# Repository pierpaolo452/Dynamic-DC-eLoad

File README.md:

# Dynamic DC eLoad
A DC electronic load with protections. It's a learning/developing project, so a lot of things are discrete just for learning to build it for example the Efuse is discrete

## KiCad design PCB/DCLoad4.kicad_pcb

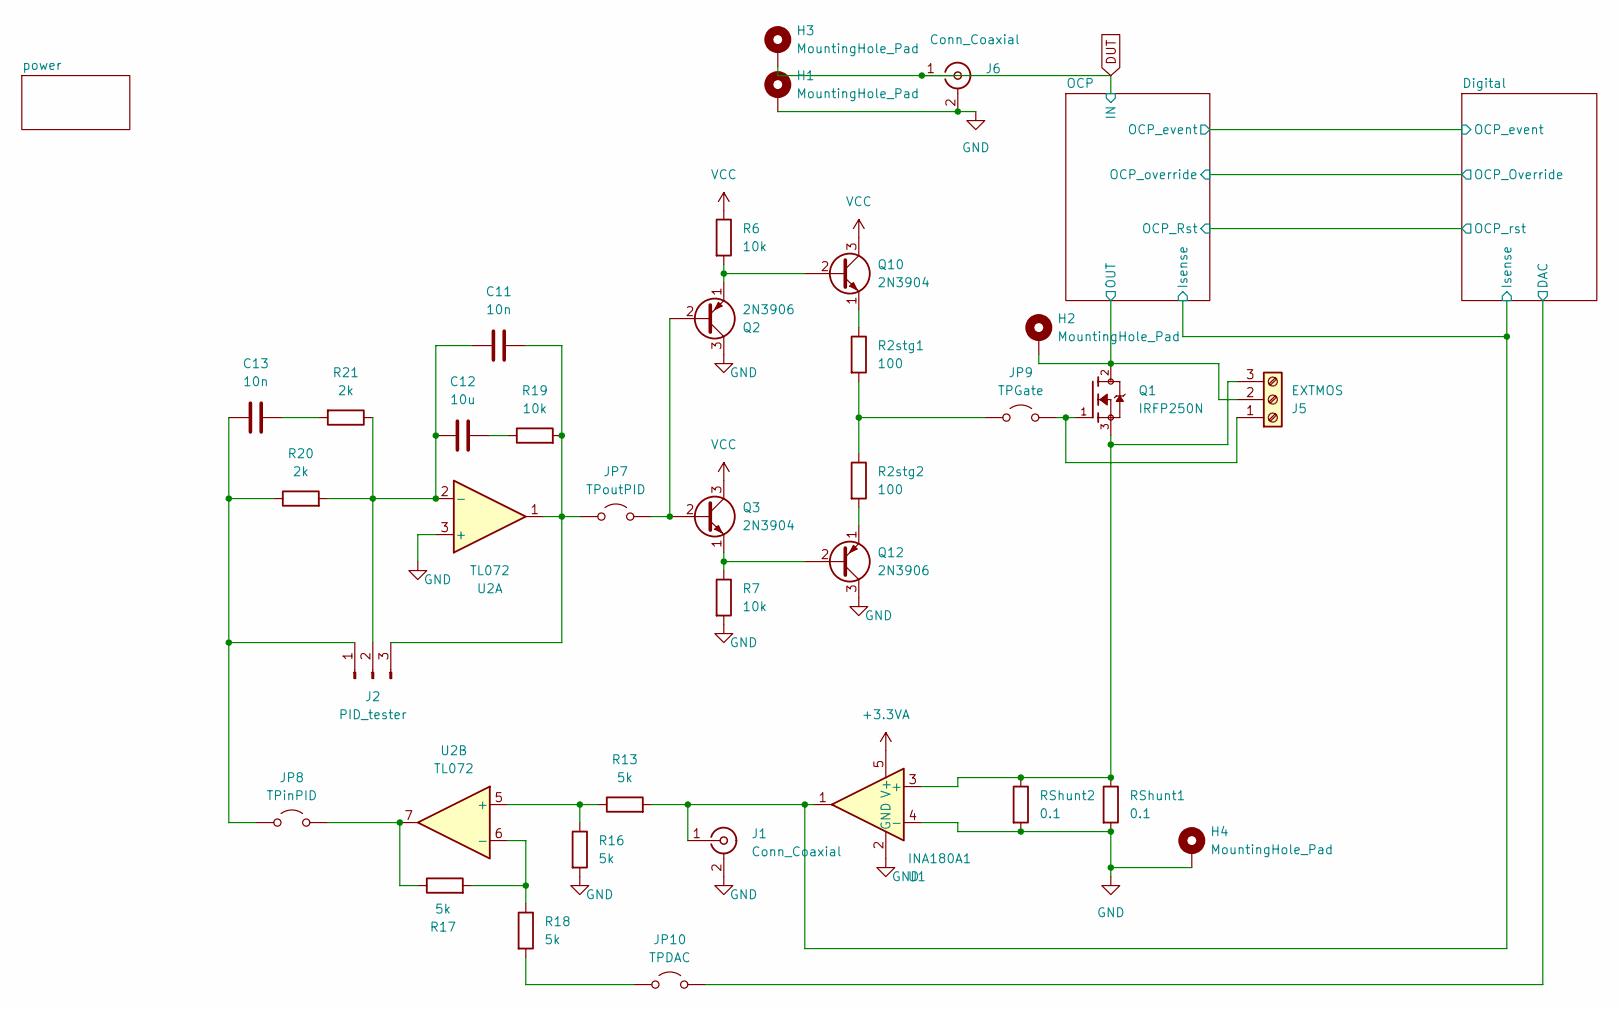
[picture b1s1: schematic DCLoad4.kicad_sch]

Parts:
C11, C13: 10n; C_0805_2012Metric_Pad1.18x1.45mm_HandSolder
C12: 10u; C_0805_2012Metric_Pad1.18x1.45mm_HandSolder
H1, H2, H3, H4: MountingHole_Pad; MountingHole_3.7mm_Pad_Via
J1, J6: Conn_Coaxial; BNC_Amphenol_B6252HB-NPP3G-50_Horizontal
J2: PID_tester; PinSocket_1x03_P2.54mm_Vertical
J5: EXTMOS; TerminalBlock_Phoenix_MKDS-1,5-3-5.08_1x03_P5.08mm_Horizont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
JP7: TPoutPID; PinSocket_1x02_P2.54mm_Vertical
JP8: TPinPID; PinSocket_1x02_P2.54mm_Vertical
JP9: TPGate; PinSocket_1x02_P2.54mm_Vertical
JP10: TPDAC; PinSocket_1x02_P2.54mm_Vertical
Q1: IRFP250N; TO-247-3_Vertical
Q2: 2N3906; SOT-23_Handsoldering
Q3: 2N3904; SOT-23_Handsoldering
Q10: 2N3904; TO-92
Q12: 2N3906; TO-92
R2stg1, R2stg2: 100; R_2512_6332Metric_Pad1.40x3.35mm_HandSolder
R6, R7, R19: 10k; R_0805_2012Metric_Pad1.20x1.40mm_HandSolder
R13, R16, R17, R18: 5k; R_0805_2012Metric_Pad1.20x1.40mm_HandSolder
R20, R21: 2k; R_0805_2012Metric_Pad1.20x1.40mm_HandSolder
RShunt1, RShunt2: 0.1; R_2512_6332Metric_Pad1.40x3.35mm_HandSolder
U1: INA180A1; SOT-23-5_HandSoldering
U2: TL072; DIP-8_W7.62mm_Socket

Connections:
+3.3VA: U1.5 (V+); also elsewhere on the board
/Digital/DAC: JP10.2 (B); also elsewhere on the board
/Digital/Isense: J1.1 (In), R13.2, U1.1; also elsewhere on the board
/OCP/OUT: H2.1, J5.2, Q1.2; also elsewhere on the board
DUT: H3.1, J6.1 (In); also elsewhere on the board
GND: H1.1, H4.1, J1.2 (Ext), J6.2 (Ext), Q2.3 (C), Q12.3 (C), R7.2, R16.2, RShunt1.2, RShunt2.2, U1.2 (GND), U1.4 (-), U2.3 (+); also elsewhere on the board
unnamed: C12.2, R19.1
unnamed: C13.2, R21.2
unnamed: C13.1, J2.1, JP8.1 (A), R20.1
unnamed: C11.1, C12.1, J2.2, R20.2, R21.1, U2.2 (-)
unnamed: C11.2, J2.3, JP7.1 (A), R19.2, U2.1
unnamed: J5.1, JP9.2 (B), Q1.1
unnamed: J5.3, Q1.3, RShunt1.1, RShunt2.1, U1.3 (+)
unnamed: JP7.2 (B), Q2.2 (B), Q3.2 (B)
unnamed: JP8.2 (B), R17.1, U2.7
unnamed: JP9.1 (A), R2stg1.2, R2stg2.1
unnamed: JP10.1 (A), R18.2
unnamed: Q2.1 (E), Q10.2 (B), R6.2
unnamed: Q10.1 (E), R2stg1.1
unnamed: Q3.1 (E), Q12.2 (B), R7.1
unnamed: Q12.1 (E), R2stg2.2
unnamed: R13.1, R16.1, U2.5 (+)
unnamed: R17.2, R18.1, U2.6 (-)
VCC: Q3.3 (C), Q10.3 (C), R6.1; also elsewhere on the board

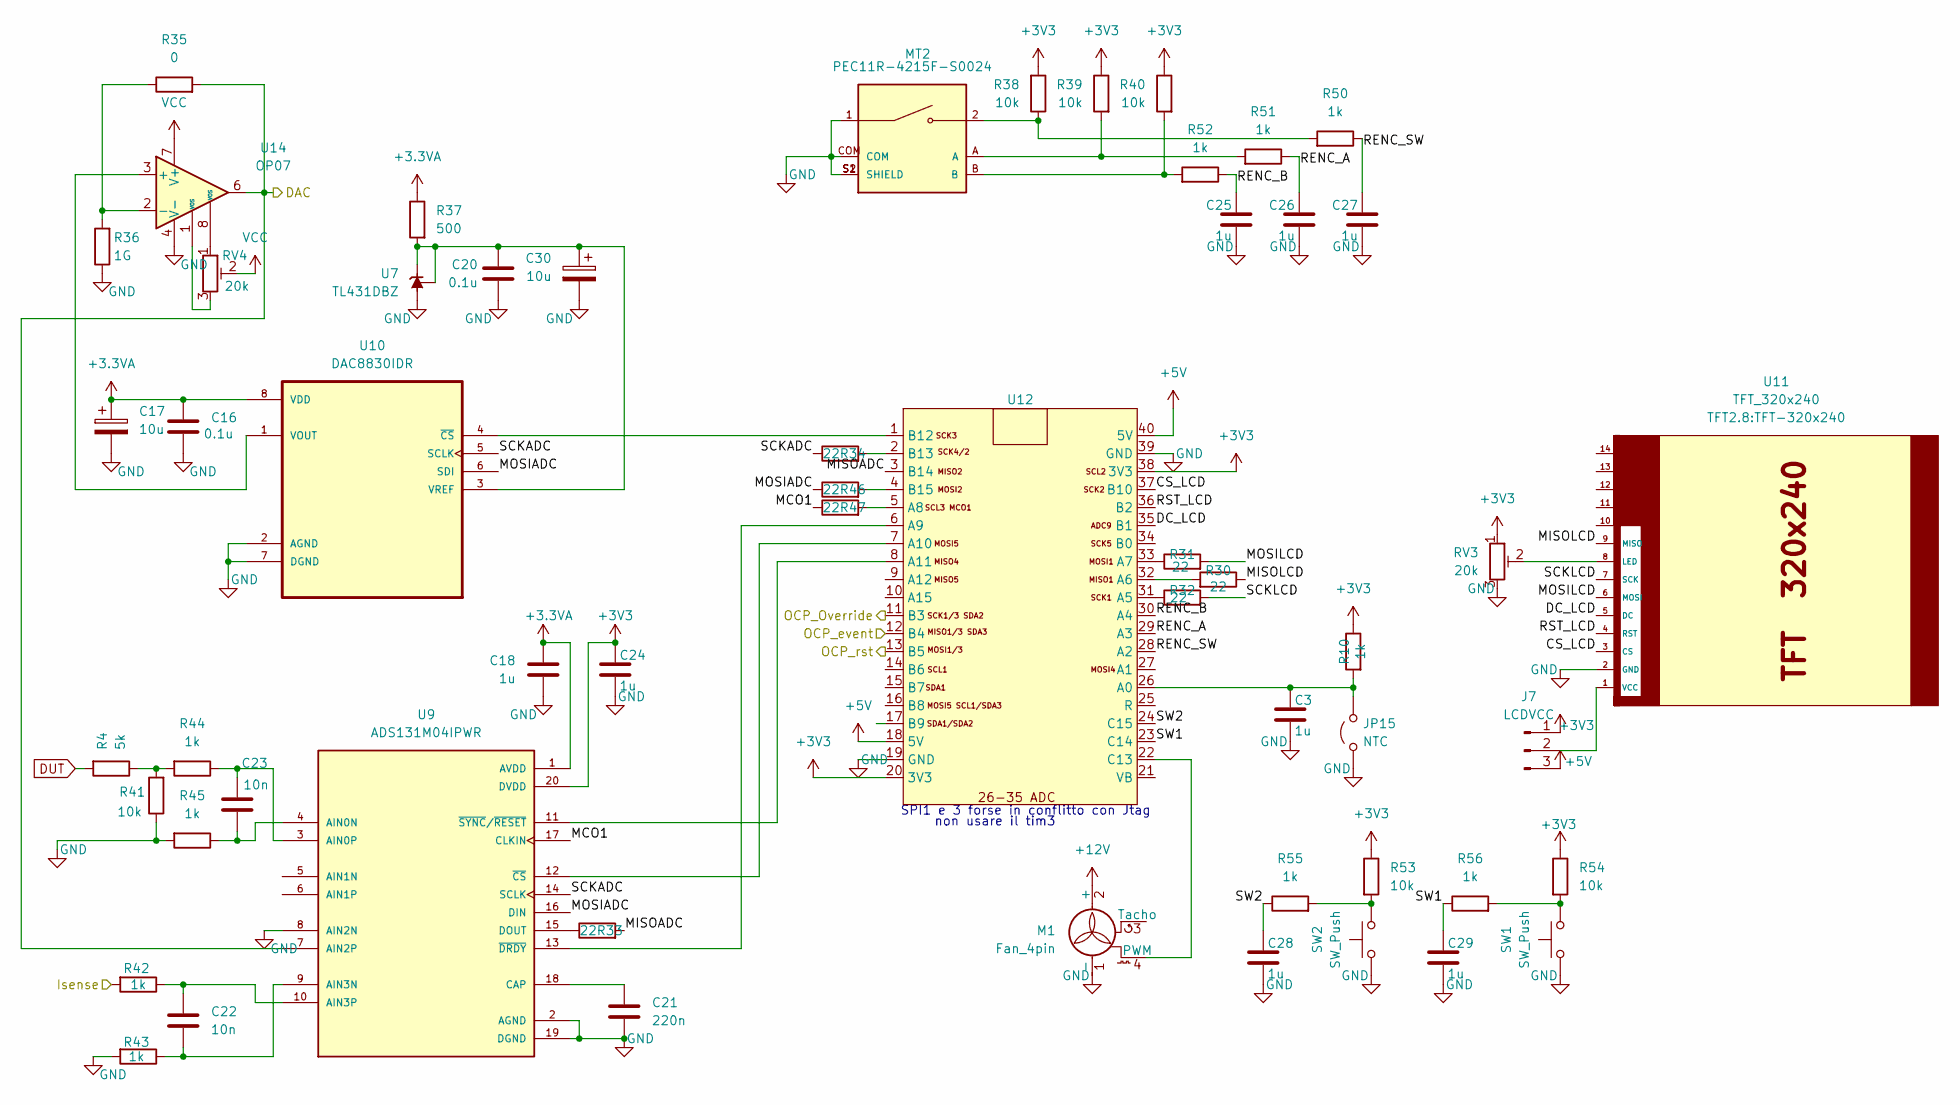
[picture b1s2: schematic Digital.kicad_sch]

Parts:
C3, C18, C24, C25, C26, C27, C28, C29: 1u; C_0805_2012Metric_Pad1.18x1.45mm_HandSolder
C16, C20: 0.1u; C_0805_2012Metric_Pad1.18x1.45mm_HandSolder
C17, C30: 10u; CP_EIA-3216-18_Kemet-A_Pad1.58x1.35mm_HandSolder
C21: 220n; C_0805_2012Metric_Pad1.18x1.45mm_HandSolder
C22, C23: 10n; C_0805_2012Metric_Pad1.18x1.45mm_HandSolder
J7: LCDVCC; PinSocket_1x03_P2.54mm_Vertical
JP15: NTC; PinSocket_1x02_P2.54mm_Vertical
M1: Fan_4pin; FanPinHeader_1x04_P2.54mm_Vertical
MT2: PEC11R-4215F-S0024; XDCR_PEC11R-4215F-S0024; PARTREV Rev. 09/19
R4: 5k; R_0805_2012Metric_Pad1.20x1.40mm_HandSolder
R10, R42, R43, R44, R45, R50, R51, R52, R55, R56: 1k; R_0805_2012Metric_Pad1.20x1.40mm_HandSolder
R30, R31, R32, R33, R34, R46, R47: 22; R_0805_2012Metric_Pad1.20x1.40mm_HandSolder
R35: 0; R_0805_2012Metric_Pad1.20x1.40mm_HandSolder
R36: 1G; R_0805_2012Metric_Pad1.20x1.40mm_HandSolder
R37: 500; R_0805_2012Metric_Pad1.20x1.40mm_HandSolder
R38, R39, R40, R41, R53, R54: 10k; R_0805_2012Metric_Pad1.20x1.40mm_HandSolder
RV3, RV4: 20k; Potentiometer_ACP_CA9-H5_Horizontal; LCSC C118929
SW1, SW2: SW_Push; Soft_Switch 8x8mm
U7: TL431DBZ; SOT-23_Handsoldering
U9: ADS131M04IPWR; TSSOP-20_4.4x6.5mm_P0.65mm; PARTREV D
U10: DAC8830IDR; SOIC127P599X175-8N
U11: TFT_320x240; TFT-320x240
U12: Blackpill_mia
U14: OP07; DIP-8_W7.62mm_Socket

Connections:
+3.3VA: C16.2, C17.1, C18.2, R37.1, U9.1 (AVDD), U10.8 (VDD); also elsewhere on the board
+3V3: C24.2, J7.1, R10.1, R38.2, R39.1, R40.1, R53.1, R54.1, RV3.1, U9.20 (DVDD), U12.20 (3V3), U12.38 (3V3); also elsewhere on the board
+5V: J7.3, U12.18 (5V), U12.40 (5V); also elsewhere on the board
+12V: M1.2 (+); also elsewhere on the board
/Digital/CS_LCD: U11.3 (CS), U12.37 (B10)
/Digital/DAC: R35.2, U9.7 (AIN2P), U14.6; also elsewhere on the board
/Digital/DC_LCD: U11.5 (DC), U12.35 (B1)
/Digital/Isense: R42.2; also elsewhere on the board
/Digital/MCO1: R47.1, U9.17 (CLKIN)
/Digital/MISOADC: R33.2, U12.3 (B14)
/Digital/MISOLCD: R30.1, U11.9 (MISO)
/Digital/MOSIADC: R46.1, U9.16 (DIN), U10.6 (SDI)
/Digital/MOSILCD: R31.2, U11.6 (MOSI)
/Digital/OCP_Override: U12.11 (B3); also elsewhere on the board
/Digital/OCP_event: U12.12 (B4); also elsewhere on the board
/Digital/OCP_rst: U12.13 (B5); also elsewhere on the board
/Digital/RENC_A: C26.2, R51.1, U12.29 (A3)
/Digital/RENC_B: C25.2, R52.1, U12.30 (A4)
/Digital/RENC_SW: C27.2, R50.1, U12.28 (A2)
/Digital/RST_LCD: U11.4 (RST), U12.36 (B2)
/Digital/SCKADC: R34.1, U9.14 (SCLK), U10.5 (SCLK)
/Digital/SCKLCD: R32.2, U11.7 (SCK)
/Digital/SW1: C29.2, R56.1, U12.23 (C14)
/Digital/SW2: C28.2, R55.1, U12.24 (C15)
DUT: R4.2; also elsewhere on the board
GND: C3.1, C16.1, C17.2, C18.1, C20.1, C21.2, C24.1, C25.1, C26.1, C27.1, C28.1, C29.1, C30.2, JP15.1 (A), M1.1 (-), MT2.1, MT2.COM, MT2.S1 (SHIELD), MT2.S2 (SHIELD), R36.1, R41.1, R43.2, R45.2, RV3.3, SW1.1, SW2.1, U7.3 (A), U9.2 (AGND), U9.8 (AIN2N), U9.19 (DGND), U10.2 (AGND), U10.7 (DGND), U11.2 (GND), U12.19 (GND), U12.39 (GND), U14.4 (V-); also elsewhere on the board
unnamed: J7.2, U11.1 (VCC)
unnamed: C3.2, JP15.2 (B), R10.2, U12.26 (A0)
unnamed: M1.4 (PWM), U12.22 (C13)
unnamed: MT2.2, R38.1, R50.2
unnamed: MT2.A, R39.2, R51.2
unnamed: MT2.B, R40.2, R52.2
unnamed: R4.1, R41.2, R44.2
unnamed: R53.2, R55.2, SW2.2
unnamed: R54.2, R56.2, SW1.2
unnamed: RV4.1, U14.8 (VOS)
unnamed: RV4.3, U14.1 (VOS)
unnamed: C23.2, R45.1, U9.4 (AIN0N)
unnamed: C23.1, R44.1, U9.3 (AIN0P)
unnamed: C22.2, R43.1, U9.9 (AIN3N)
unnamed: C22.1, R42.1, U9.10 (AIN3P)
unnamed: C21.1, U9.18 (CAP)
unnamed: R33.1, U9.15 (DOUT)
unnamed: U10.1 (VOUT), U14.3 (+)
unnamed: C20.2, C30.1, R37.2, U7.1 (K), U7.2 (REF), U10.3 (VREF)
unnamed: U10.4 (~CS), U12.1 (B12)
unnamed: RV3.2, U11.8 (LED)
unnamed: R32.1, U12.31 (A5)
unnamed: R30.2, U12.32 (A6)
unnamed: R31.1, U12.33 (A7)
unnamed: R47.2, U12.5 (A8)
unnamed: U9.13 (~DRDY), U12.6 (A9)
unnamed: U9.12 (~CS), U12.7 (A10)
unnamed: U9.11 (~SYNC/~RESET), U12.8 (A11)
unnamed: R34.2, U12.2 (B13)
unnamed: R46.2, U12.4 (B15)
unnamed: R35.1, R36.2, U14.2 (-)
VCC: RV4.2, U14.7 (V+); also elsewhere on the board

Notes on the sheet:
SPI1 e 3 forse in conflitto con Jtag
non usare il tim3

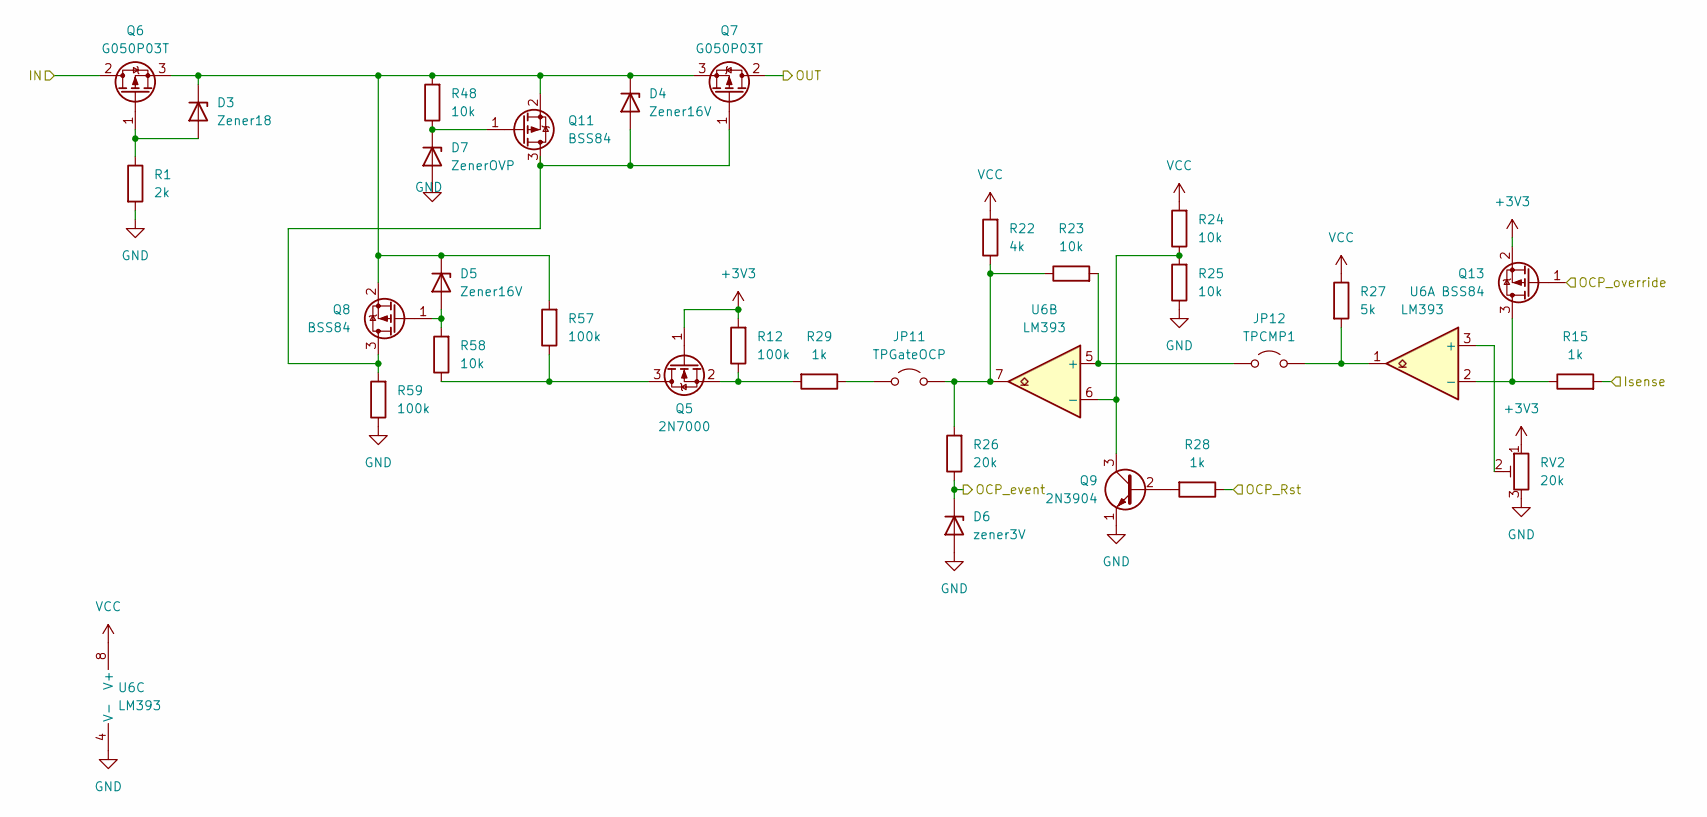
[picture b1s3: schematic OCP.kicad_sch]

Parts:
D3: Zener18; D_DO-35_SOD27_P7.62mm_Horizontal
D4, D5: Zener16V; D_DO-35_SOD27_P7.62mm_Horizontal
D6: zener3V; D_DO-35_SOD27_P7.62mm_Horizontal
D7: ZenerOVP; D_DO-35_SOD27_P7.62mm_Horizontal
JP11: TPGateOCP; PinSocket_1x02_P2.54mm_Vertical
JP12: TPCMP1; PinSocket_1x02_P2.54mm_Vertical
Q5: 2N7000; SOT-23_Handsoldering
Q6, Q7: G050P03T; TO-220-3_Vertical
Q8, Q11, Q13: BSS84; SOT-23_Handsoldering
Q9: 2N3904; SOT-23_Handsoldering
R1: 2k; R_0805_2012Metric_Pad1.20x1.40mm_HandSolder
R12, R57, R59: 100k; R_0805_2012Metric_Pad1.20x1.40mm_HandSolder
R15, R28, R29: 1k; R_0805_2012Metric_Pad1.20x1.40mm_HandSolder
R22: 4k; R_0805_2012Metric_Pad1.20x1.40mm_HandSolder
R23, R24, R25, R48, R58: 10k; R_0805_2012Metric_Pad1.20x1.40mm_HandSolder
R26: 20k; R_0805_2012Metric_Pad1.20x1.40mm_HandSolder
R27: 5k; R_0805_2012Metric_Pad1.20x1.40mm_HandSolder
RV2: 20k; Potentiometer_ACP_CA9-H5_Horizontal; LCSC C118929
U6: LM393; SOIC-8_3.9x4.9mm_P1.27mm

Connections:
+3V3: Q5.1 (G), Q13.2 (S), R12.2, RV2.1; also elsewhere on the board
/Digital/Isense: R15.2; also elsewhere on the board
/Digital/OCP_Override: Q13.1 (G); also elsewhere on the board
/Digital/OCP_event: D6.1 (K), R26.1; also elsewhere on the board
/Digital/OCP_rst: R28.1; also elsewhere on the board
/OCP/OUT: Q7.2 (D); also elsewhere on the board
DUT: Q6.2 (D); also elsewhere on the board
GND: D6.2 (A), D7.2 (A), Q9.1 (E), R1.2, R25.1, R59.1, RV2.3, U6.4 (V-); also elsewhere on the board
unnamed: D3.2 (A), Q6.1 (G), R1.1
unnamed: D3.1 (K), D4.1 (K), D5.1 (K), Q6.3 (S), Q7.3 (S), Q8.2 (S), Q11.2 (S), R48.2, R57.2
unnamed: D4.2 (A), Q7.1 (G), Q8.3 (D), Q11.3 (D), R59.2
unnamed: D5.2 (A), Q8.1 (G), R58.2
unnamed: D7.1 (K), Q11.1 (G), R48.1
unnamed: JP11.1 (A), R29.1
unnamed: JP11.2 (B), R22.1, R23.1, R26.2, U6.7
unnamed: JP12.1 (A), R23.2, U6.5 (+)
unnamed: JP12.2 (B), R27.2, U6.1
unnamed: Q5.3 (D), R57.1, R58.1
unnamed: Q5.2 (S), R12.1, R29.2
unnamed: Q9.2 (B), R28.2
unnamed: Q9.3 (C), R24.1, R25.2, U6.6 (-)
unnamed: Q13.3 (D), R15.1, U6.2 (-)
unnamed: RV2.2, U6.3 (+)
VCC: R22.2, R24.2, R27.1, U6.8 (V+); also elsewhere on the board

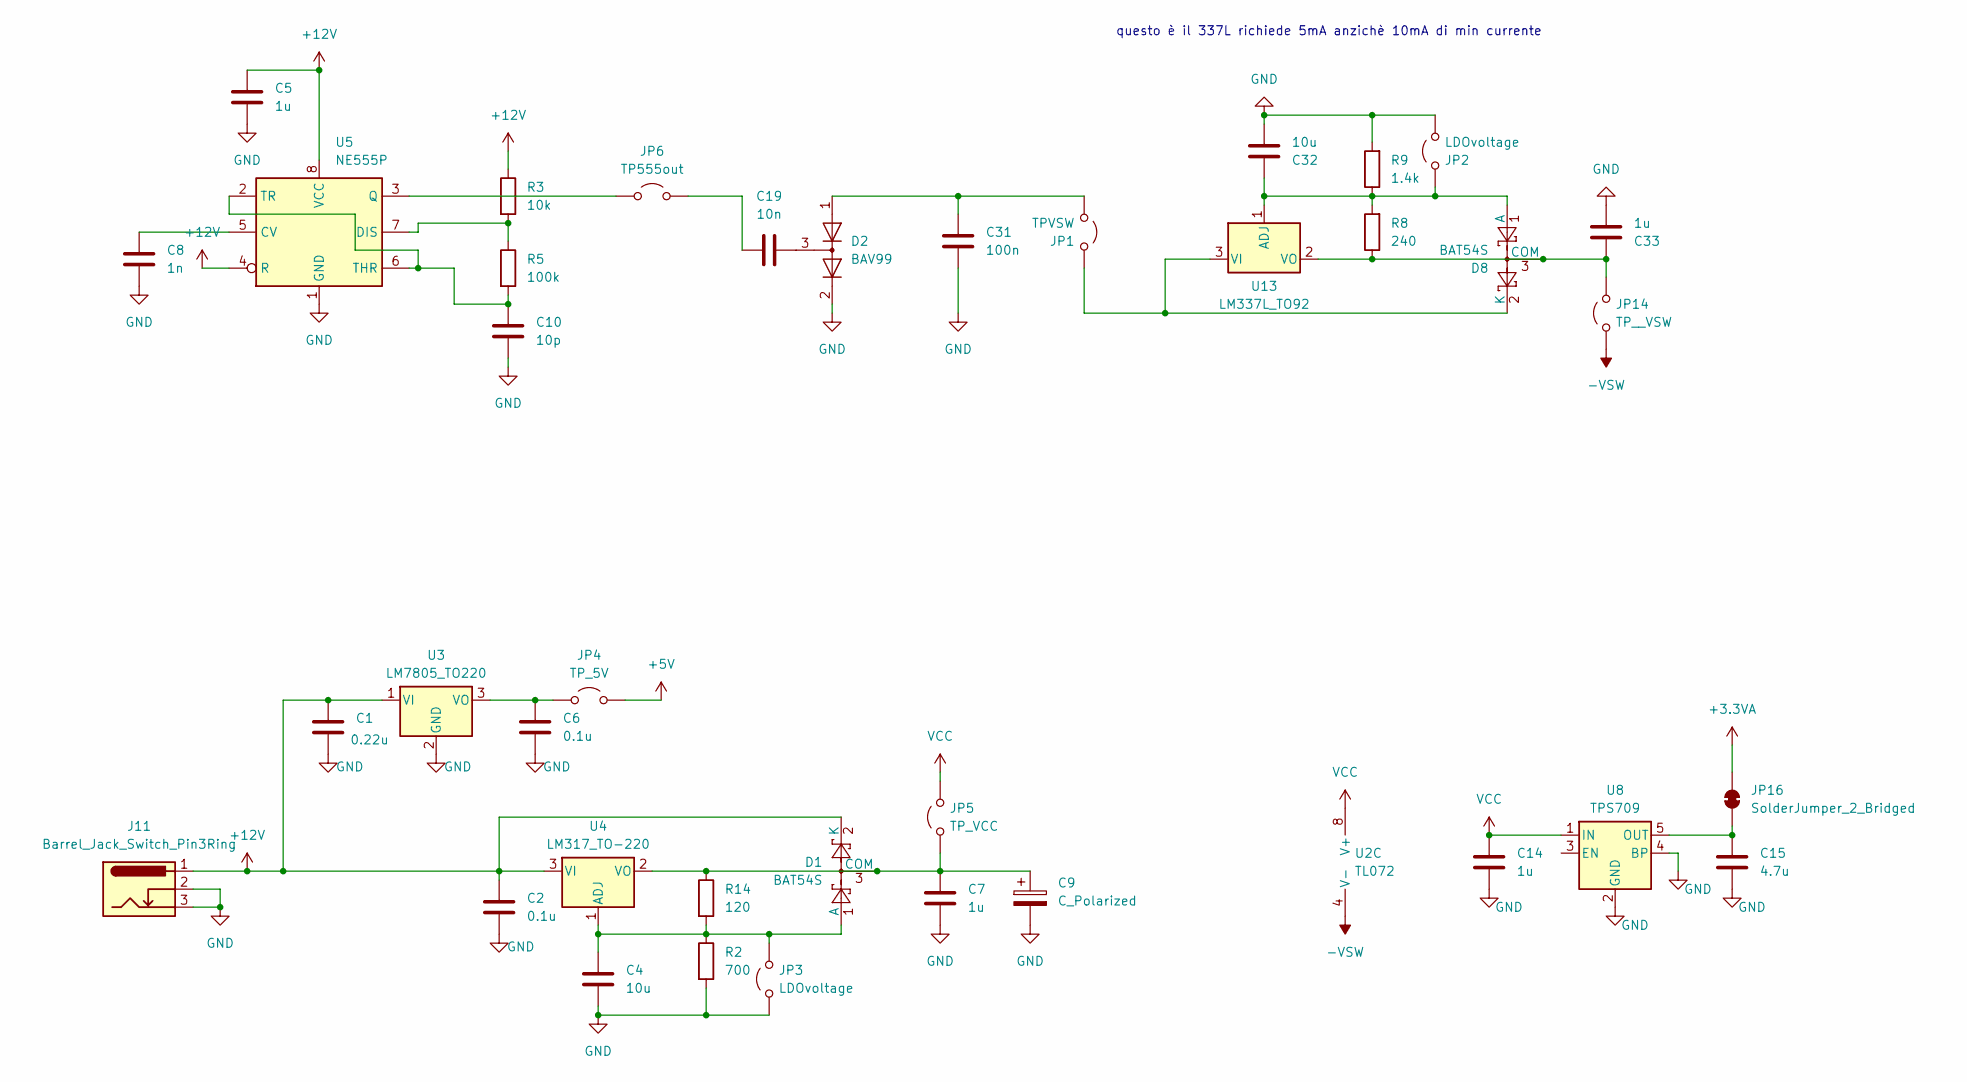
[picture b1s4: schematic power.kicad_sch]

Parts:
C1: 0.22u; C_0805_2012Metric_Pad1.18x1.45mm_HandSolder
C2, C6: 0.1u; C_0805_2012Metric_Pad1.18x1.45mm_HandSolder
C4, C32: 10u; C_0805_2012Metric_Pad1.18x1.45mm_HandSolder
C5, C7, C14, C33: 1u; C_0805_2012Metric_Pad1.18x1.45mm_HandSolder
C8: 1n; C_0805_2012Metric_Pad1.18x1.45mm_HandSolder
C9: C_Polarized; C_Radial_D5.0mm_H11.0mm_P2.00mm
C10: 10p; C_0805_2012Metric_Pad1.18x1.45mm_HandSolder
C15: 4.7u; C_0805_2012Metric_Pad1.18x1.45mm_HandSolder
C19: 10n; C_0805_2012Metric_Pad1.18x1.45mm_HandSolder
C31: 100n; C_0805_2012Metric_Pad1.18x1.45mm_HandSolder
D1, D8: BAT54S; SOT-23
D2: BAV99; SOT-23_Handsoldering
J11: Barrel_Jack_Switch_Pin3Ring; BarrelJack_Kycon_KLDX-0202-xC_Horizontal
JP1: TPVSW; PinSocket_1x02_P2.54mm_Vertical
JP2, JP3: LDOvoltage; PinSocket_1x02_P2.54mm_Vertical
JP4: TP_5V; PinSocket_1x02_P2.54mm_Vertical
JP5: TP_VCC; PinSocket_1x02_P2.54mm_Vertical
JP6: TP555out; PinSocket_1x02_P2.54mm_Vertical
JP14: TP__VSW; PinSocket_1x02_P2.54mm_Vertical
JP16: SolderJumper_2_Bridged; SolderJumper-2_P1.3mm_Bridged_RoundedPad1.0x1.5mm
R2: 700; R_0805_2012Metric_Pad1.20x1.40mm_HandSolder
R3: 10k; R_0805_2012Metric_Pad1.20x1.40mm_HandSolder
R5: 100k; R_0805_2012Metric_Pad1.20x1.40mm_HandSolder
R8: 240; R_0805_2012Metric_Pad1.20x1.40mm_HandSolder
R9: 1.4k; R_0805_2012Metric_Pad1.20x1.40mm_HandSolder
R14: 120; R_0805_2012Metric_Pad1.20x1.40mm_HandSolder
U2: TL072; DIP-8_W7.62mm_Socket
U3: LM7805_TO220; TO-220-3_Vertical
U4: LM317_TO-220; TO-220-3_Vertical
U5: NE555P; DIP-8_W7.62mm
U8: TPS709; SOT-23-5_HandSoldering
U13: LM337L_TO92; TO-92

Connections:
+3.3VA: JP16.2 (B); also elsewhere on the board
+5V: JP4.2 (B); also elsewhere on the board
+12V: C1.1, C2.1, C5.1, D1.2 (K), J11.1, R3.1, U3.1 (VI), U4.3 (VI), U5.4 (R), U5.8 (VCC); also elsewhere on the board
-VSW: JP14.2 (B), U2.4 (V-)
GND: C1.2, C2.2, C4.2, C5.2, C6.2, C7.2, C8.2, C9.2, C10.2, C14.2, C15.2, C31.2, C32.2, C33.2, D2.2 (A), J11.2, J11.3, JP2.1 (A), JP3.1 (A), R2.2, R9.2, U3.2 (GND), U5.1 (GND), U8.2 (GND), U8.4 (BP); also elsewhere on the board
unnamed: C19.2, D2.3 (K)
unnamed: C4.1, D1.1 (A), JP3.2 (B), R2.1, R14.2, U4.1 (ADJ)
unnamed: C7.1, C9.1, D1.3 (COM), JP5.1 (A), R14.1, U4.2 (VO)
unnamed: C32.1, D8.1 (A), JP2.2 (B), R8.2, R9.1, U13.1 (ADJ)
unnamed: C33.1, D8.3 (COM), JP14.1 (A), R8.1, U13.2 (VO)
unnamed: D8.2 (K), JP1.2 (B), U13.3 (VI)
unnamed: C31.1, D2.1 (K), JP1.1 (A)
unnamed: C6.1, JP4.1 (A), U3.3 (VO)
unnamed: JP6.1 (A), U5.3 (Q)
unnamed: C19.1, JP6.2 (B)
unnamed: C15.1, JP16.1 (A), U8.5 (OUT)
unnamed: C8.1, U5.5 (CV)
unnamed: R3.2, R5.1, U5.7 (DIS)
unnamed: C10.1, R5.2, U5.2 (TR), U5.6 (THR)
VCC: C14.1, JP5.2 (B), U2.8 (V+), U8.1 (IN); also elsewhere on the board

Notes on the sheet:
questo è il 337L richiede 5mA anzichè 10mA di min currente

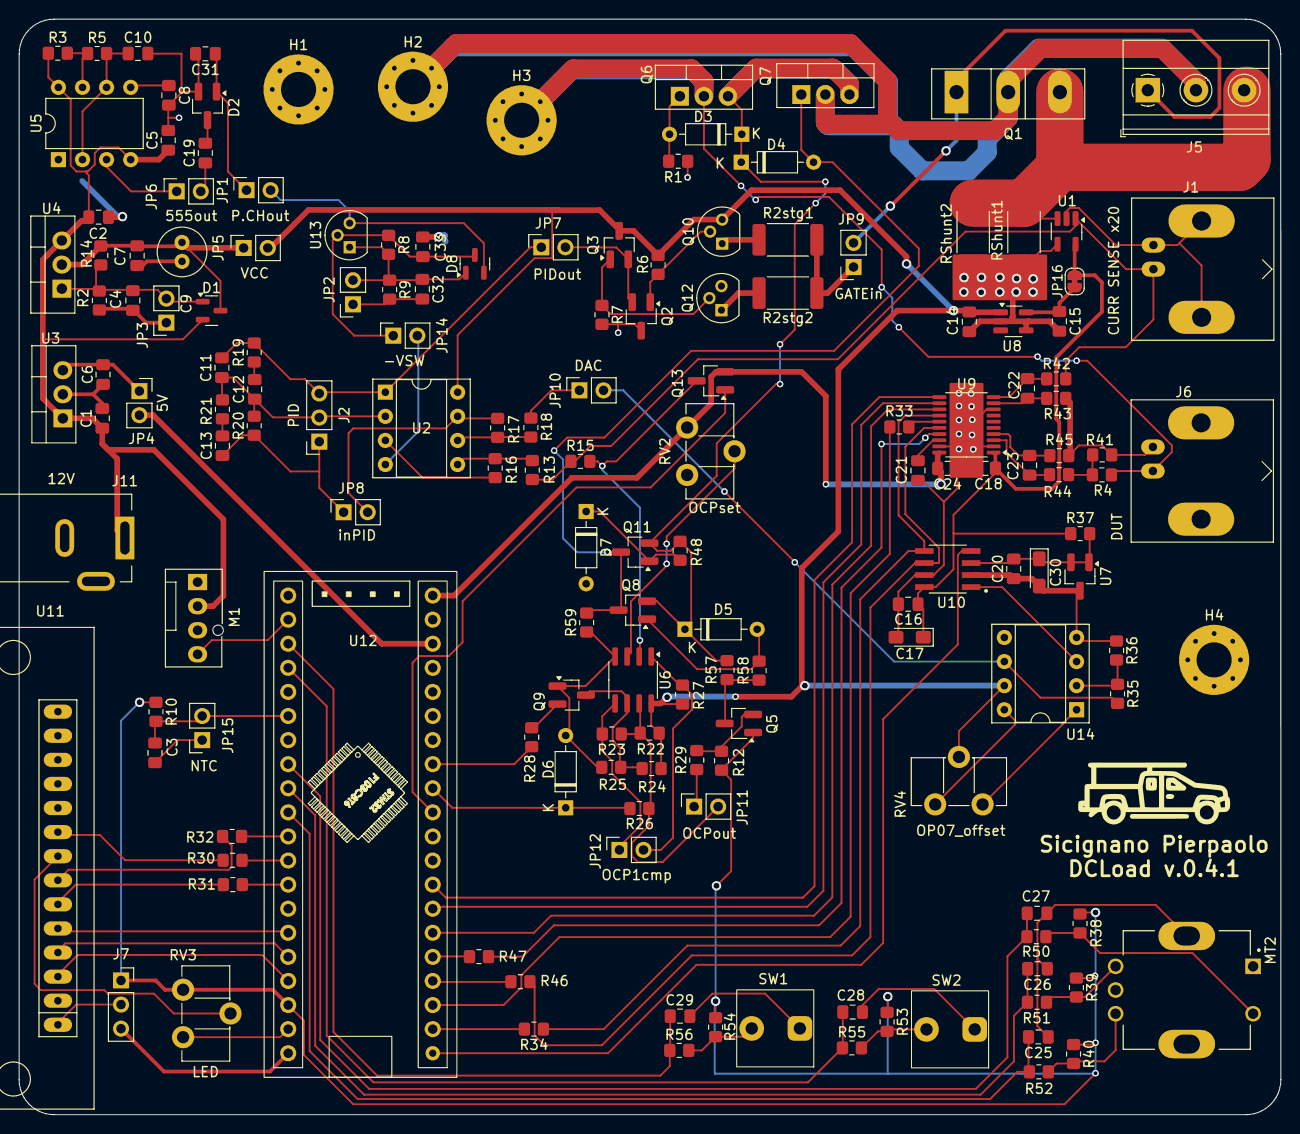
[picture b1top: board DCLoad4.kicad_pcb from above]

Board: 2 copper layers, 133.0 x 115.5 mm, 160 parts (0 on the bottom side), 106 nets.

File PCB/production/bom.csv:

Designator,Footprint,Quantity,Value,LCSC Part #
C1,0805,1,0.22u,
"C10, C8",0805,2,1n,
"C11, C13, C19, C22, C23",0805,5,10n,
"C12, C32, C4",0805,3,10u,
"C14, C18, C24, C25, C26, C27, C28, C29, C3, C33, C5, C7",0805,12,1u,
C15,0805,1,4.7u,
"C16, C2, C20, C6",0805,4,0.1u,
"C17, C30",CP_EIA-3216-18_Kemet-A_Pad1.58x1.35mm_HandSolder,2,10u,
C21,0805,1,220n,
C31,0805,1,100n,
C9,C_Radial_D5.0mm_H11.0mm_P2.00mm,1,C_Polarized,
"D1, D8",SOT-23,2,BAT54S,
D2,SOT-23_Handsoldering,1,BAV99,
D3,D_DO-35_SOD27_P7.62mm_Horizontal,1,Zener18,
"D4, D5",D_DO-35_SOD27_P7.62mm_Horizontal,2,Zener16V,
D6,D_DO-35_SOD27_P7.62mm_Horizontal,1,zener3V,
D7,D_DO-35_SOD27_P7.62mm_Horizontal,1,ZenerOVP,
"J1, J6",BNC_Amphenol_B6252HB-NPP3G-50_Horizontal,2,Conn_Coaxial,
J11,BarrelJack_Kycon_KLDX-0202-xC_Horizontal,1,Barrel_Jack_Switch_Pin3Ring,
J2,PinSocket_1x03_P2.54mm_Vertical,1,PID_tester,
J5,"TerminalBlock_Phoenix_MKDS-1,5-3-5.08_1x03_P5.08mm_Horizontal",1,EXTMOS,
J7,PinSocket_1x03_P2.54mm_Vertical,1,LCDVCC,
JP1,PinSocket_1x02_P2.54mm_Vertical,1,TPVSW,
JP10,PinSocket_1x02_P2.54mm_Vertical,1,TPDAC,
JP11,PinSocket_1x02_P2.54mm_Vertical,1,TPGateOCP,
JP12,PinSocket_1x02_P2.54mm_Vertical,1,TPCMP1,
JP14,PinSocket_1x02_P2.54mm_Vertical,1,TP__VSW,
JP15,PinSocket_1x02_P2.54mm_Vertical,1,NTC,
"JP2, JP3",PinSocket_1x02_P2.54mm_Vertical,2,LDOvoltage,
JP4,PinSocket_1x02_P2.54mm_Vertical,1,TP_5V,
JP5,PinSocket_1x02_P2.54mm_Vertical,1,TP_VCC,
JP6,PinSocket_1x02_P2.54mm_Vertical,1,TP555out,
JP7,PinSocket_1x02_P2.54mm_Vertical,1,TPoutPID,
JP8,PinSocket_1x02_P2.54mm_Vertical,1,TPinPID,
JP9,PinSocket_1x02_P2.54mm_Vertical,1,TPGate,
M1,FanPinHeader_1x04_P2.54mm_Vertical,1,Fan_4pin,
MT2,XDCR_PEC11R-4215F-S0024,1,PEC11R-4215F-S0024,
Q1,TO-247-3_Vertical,1,IRFP250N,
Q10,TO-92,1,2N3904,
"Q11, Q13, Q8",SOT-23_Handsoldering,3,BSS84,
Q12,TO-92,1,2N3906,
Q2,SOT-23_Handsoldering,1,2N3906,
"Q3, Q9",SOT-23_Handsoldering,2,2N3904,
Q5,SOT-23_Handsoldering,1,2N7000,
"Q6, Q7",TO-220-3_Vertical,2,G050P03T,
"R1, R20, R21",0805,3,2k,
"R10, R15, R28, R29, R42, R43, R44, R45, R5, R50, R51, R52, R55, R56",0805,14,1k,
"R12, R57, R59",0805,3,100k,
"R13, R16, R17, R18, R27, R4",0805,6,5k,
R14,0805,1,120	,
"R19, R23, R24, R25, R38, R39, R40, R41, R48, R53, R54, R58, R6, R7",0805,14,10k,
R2,0805,1,700,
R22,0805,1,4k,
R26,0805,1,20k,
"R2stg1, R2stg2",2512,2,100,
R3,0805,1,100,
"R30, R31, R32, R33, R34, R46, R47",0805,7,22,
R35,0805,1,0,
R36,0805,1,1G,
R37,0805,1,500,
R8,0805,1,240,
R9,0805,1,1.4k,
"RShunt1, RShunt2",2512,2,0.1,
"RV2, RV3, RV4",Potentiometer_ACP_CA9-H5_Horizontal,3,20k,C118929
"SW1, SW2",Soft_Switch 8x8mm,2,SW_Push,
U1,SOT-23-5_HandSoldering,1,INA180A1,
U10,SOIC127P599X175-8N,1,DAC8830IDR,
U11,TFT-320x240,1,TFT_320x240,
U12,Blackpill_mia,1,~,
U13,TO-92,1,LM337L_TO92,
U14,DIP-8_W7.62mm_Socket,1,OP07,
U2,DIP-8_W7.62mm_Socket,1,TL072,
U3,TO-220-3_Vertical,1,LM7805_TO220,
U4,TO-220-3_Vertical,1,LM317_TO-220,
U5,DIP-8_W7.62mm,1,NE555P,
U6,SOIC-8_3.9x4.9mm_P1.27mm,1,LM393,
U7,SOT-23_Handsoldering,1,TL431DBZ,
U8,SOT-23-5_HandSoldering,1,TPS709,
U9,TSSOP-20_4.4x6.5mm_P0.65mm,1,ADS131M04IPWR,

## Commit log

2025-09-29 First up
2025-09-29 PCB up
    add pcb
